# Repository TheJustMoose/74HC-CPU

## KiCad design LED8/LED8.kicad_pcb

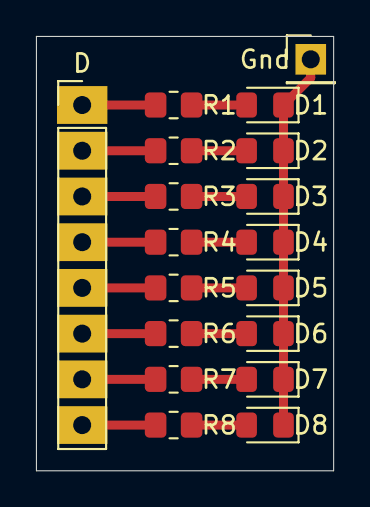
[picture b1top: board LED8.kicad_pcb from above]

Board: 2 copper layers, 16.5 x 24.1 mm, 18 parts (0 on the bottom side), 17 nets.

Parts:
D: Conn_01x08_Male; PinHeader_1x08_P2.54mm_Vertical
D1, D2, D3, D4, D5, D6, D7, D8: LED; LED_0805_2012Metric_Pad1.15x1.40mm_HandSolder
Gnd: Conn_01x01_Male; PinHeader_1x01_P2.54mm_Vertical
R1, R2, R3, R4, R5, R6, R7, R8: 1k; R_0805_2012Metric_Pad1.20x1.40mm_HandSolder

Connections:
unnamed: D1.1, D2.1, D3.1, D4.1, D5.1, D6.1, D7.1, D8.1, Gnd.1
unnamed: D1.2, R1.1
unnamed: D2.2, R2.1
unnamed: D3.2, R3.1
unnamed: D4.2, R4.1
unnamed: D5.2, R5.1
unnamed: D6.2, R6.1
unnamed: D7.2, R7.1
unnamed: D8.2, R8.1
unnamed: D.1, R1.2
unnamed: D.2, R2.2
unnamed: D.3, R3.2
unnamed: D.4, R4.2
unnamed: D.5, R5.2
unnamed: D.6, R6.2
unnamed: D.7, R7.2
unnamed: D.8, R8.2

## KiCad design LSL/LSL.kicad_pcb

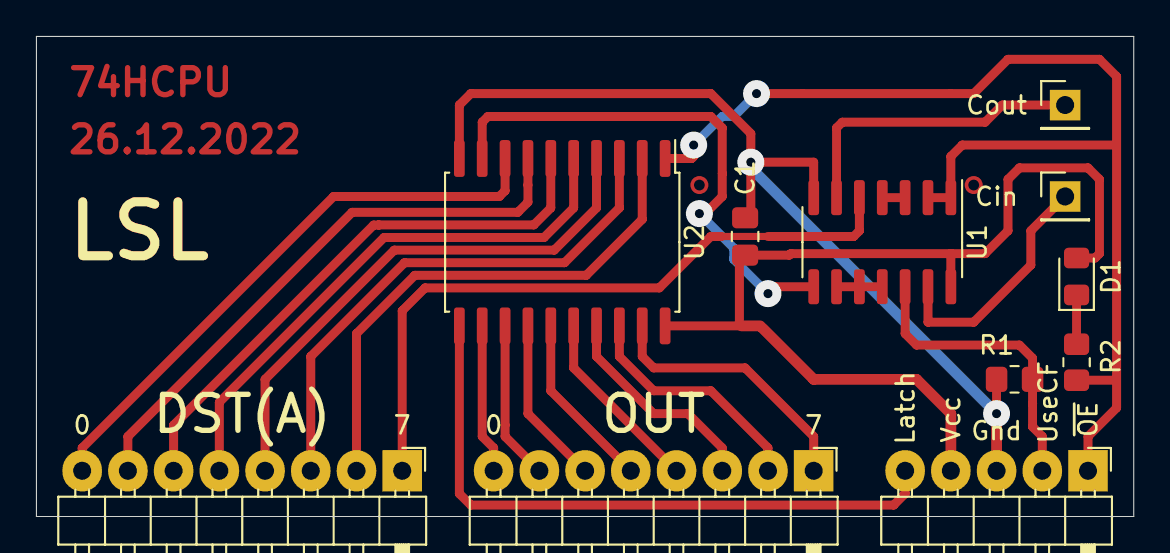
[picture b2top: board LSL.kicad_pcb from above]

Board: 2 copper layers, 61.0 x 26.7 mm, 11 parts (0 on the bottom side), 27 nets.

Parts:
C1: 0.1uF; C_0805_2012Metric_Pad1.18x1.45mm_HandSolder
D1: LED; LED_0805_2012Metric_Pad1.15x1.40mm_HandSolder
J1, J4: Conn_01x01_Male; PinHeader_1x01_P2.54mm_Vertical
J2, J3: Conn_01x08_Male; PinHeader_1x08_P2.54mm_Horizontal
J5: Conn_01x05_Male; PinHeader_1x05_P2.54mm_Horizontal
R1, R2: R; R_0805_2012Metric_Pad1.20x1.40mm_HandSolder
U1: 74HC00; SO-14_3.9x8.65mm_P1.27mm
U2: 74LS573; SOIC-20W_7.5x12.8mm_P1.27mm

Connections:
/CF_IN: J4.1, U1.13
/D0: J2.8, U2.8
/D1: J2.7, U2.7
/D2: J2.6, U2.6
/D3: J2.5, U2.5
/D4: J2.4, U2.4
/D5: J2.3, U2.3
/D6: J2.2, U2.2
/D7: J2.1, U1.5
/Latch: J5.5, U2.11
/O0: J3.8, U2.12
/O1: J3.7, U2.13
/O2: J3.6, U2.14
/O3: J3.5, U2.15
/O4: J3.4, U2.16
/O5: J3.3, U2.17
/O6: J3.2, U2.18
/O7: J3.1, U2.19
/UseCF: J5.2, R1.1, U1.12
/~(CF&OE): J1.1, U1.6
/~OE: J5.1, R2.2, U1.1, U1.2, U2.1
GND: C1.2, J5.3, R1.2, U1.7, U2.10
unnamed: D1.1, R2.1
unnamed: U1.3, U1.4
unnamed: U1.8, U2.9
unnamed: U1.9, U1.10, U1.11
VCC: C1.1, D1.2, J5.4, U1.14, U2.20

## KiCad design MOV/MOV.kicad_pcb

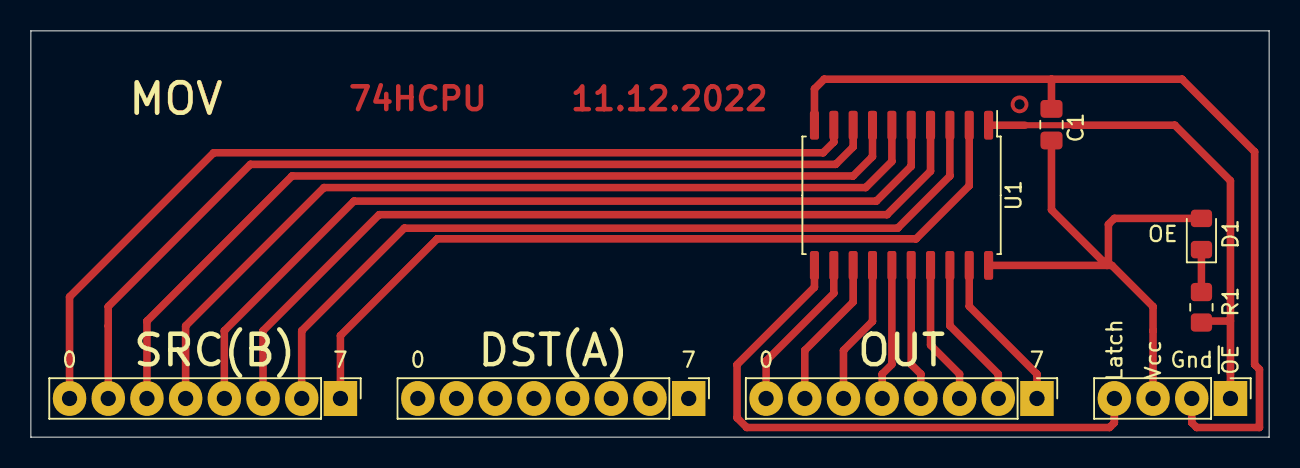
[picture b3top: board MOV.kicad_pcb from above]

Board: 2 copper layers, 81.3 x 26.7 mm, 8 parts (0 on the bottom side), 21 nets.

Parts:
C1: 0.1uF; C_0805_2012Metric_Pad1.18x1.45mm_HandSolder
D1: LED; LED_0805_2012Metric_Pad1.15x1.40mm_HandSolder
J1, J2, J3: Conn_01x08_Male; PinHeader_1x08_P2.54mm_Vertical
J4: Conn_01x04_Male; PinHeader_1x04_P2.54mm_Vertical
R1: 1k; R_0805_2012Metric_Pad1.20x1.40mm_HandSolder
U1: 74LS573; SOP-20_7.5x12.8mm_P1.27mm

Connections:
/B0: J1.8, U1.9
/B7: J1.1, U1.2
/Latch: J4.4, U1.11
/OUT0: J3.8, U1.12
/OUT7: J3.1, U1.19
/~OE: J4.1, R1.2, U1.1
GND: C1.2, J4.2, U1.10
unnamed: D1.1, R1.1
unnamed: J1.2, U1.3
unnamed: J1.3, U1.4
unnamed: J1.4, U1.5
unnamed: J1.5, U1.6
unnamed: J1.6, U1.7
unnamed: J1.7, U1.8
unnamed: J3.2, U1.18
unnamed: J3.3, U1.17
unnamed: J3.4, U1.16
unnamed: J3.5, U1.15
unnamed: J3.6, U1.14
unnamed: J3.7, U1.13
VCC: C1.1, D1.2, J4.3, U1.20

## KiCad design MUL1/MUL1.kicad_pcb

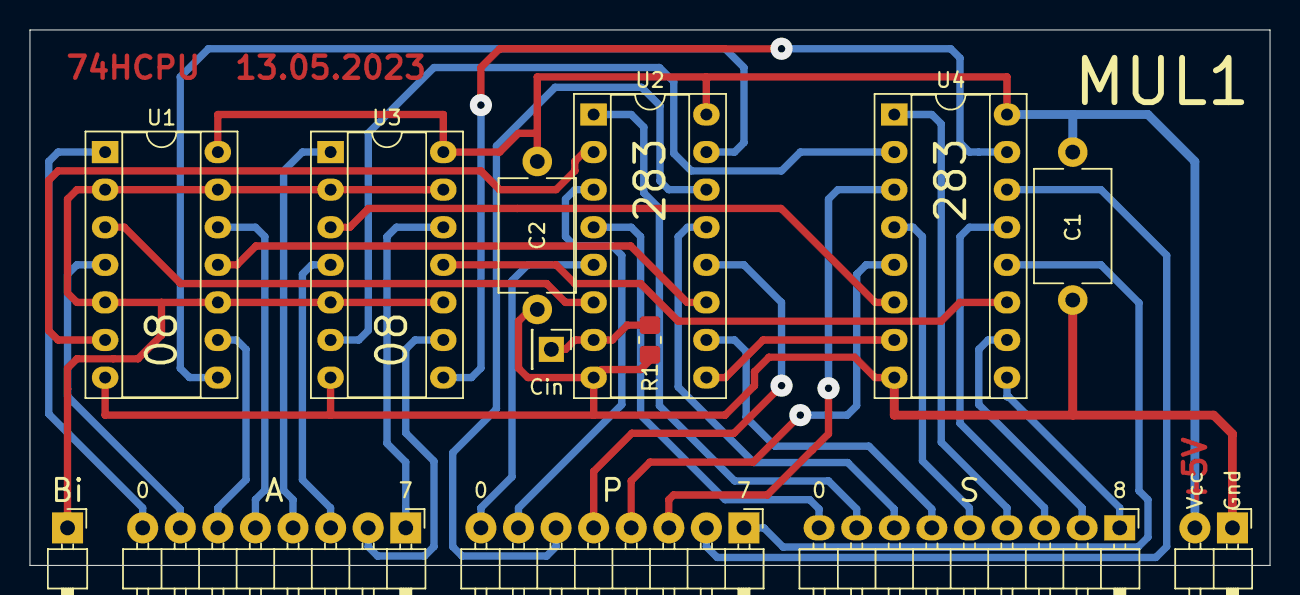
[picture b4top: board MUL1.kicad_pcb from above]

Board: 2 copper layers, 83.8 x 36.2 mm, 13 parts (0 on the bottom side), 38 nets.

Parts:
C1, C2: 0.1uF; C_Disc_D7.5mm_W5.0mm_P10.00mm
J1, J3: Conn_01x08_Male; PinHeader_1x08_P2.54mm_Horizontal
J2: Conn_01x09_Male; PinHeader_1x09_P2.54mm_Horizontal
J4: Conn_01x01_Male; PinHeader_1x01_P2.54mm_Horizontal
J5: Conn_01x02_Male; PinHeader_1x02_P2.54mm_Horizontal
J6: Conn_01x01_Male; PinHeader_1x01_P2.54mm_Vertical
R1: 10k; R_0805_2012Metric_Pad1.20x1.40mm_HandSolder
U1, U3: 74LS08; DIP-14_W7.62mm_Socket
U2, U4: 74LS283; DIP-16_W7.62mm_Socket

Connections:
/A0: J3.8, U1.1
/A1: J3.7, U1.4
/A2: J3.6, U1.9
/A3: J3.5, U1.12
/A4: J3.4, U3.1
/A5: J3.3, U3.4
/A6: J3.2, U3.9
/A7: J3.1, U3.12
/Bi: J4.1, U1.2, U1.5, U1.10, U1.13, U3.2, U3.5, U3.10, U3.13
/P0: J1.8, U2.5
/P1: J1.7, U2.3
/P2: J1.6, U2.14
/P3: J1.5, U2.12
/P4: J1.4, U4.5
/P5: J1.3, U4.3
/P6: J1.2, U4.14
/P7: J1.1, U4.12
/S0: J2.9, U2.4
/S1: J2.8, U2.1
/S2: J2.7, U2.13
/S3: J2.6, U2.10
/S4: J2.5, U4.4
/S5: J2.4, U4.1
/S6: J2.3, U4.13
/S7: J2.2, U4.10
/S8: J2.1, U4.9
GND: C1.2, C2.2, J5.1, R1.1, U1.7, U2.8, U3.7, U4.8
unnamed: J6.1, R1.2, U2.7
unnamed: U1.3, U2.6
unnamed: U1.6, U2.2
unnamed: U1.8, U2.15
unnamed: U1.11, U2.11
unnamed: U2.9, U4.7
unnamed: U3.3, U4.6
unnamed: U3.6, U4.2
unnamed: U3.8, U4.15
unnamed: U3.11, U4.11
VCC: C1.1, C2.1, J5.2, U1.14, U2.16, U3.14, U4.16

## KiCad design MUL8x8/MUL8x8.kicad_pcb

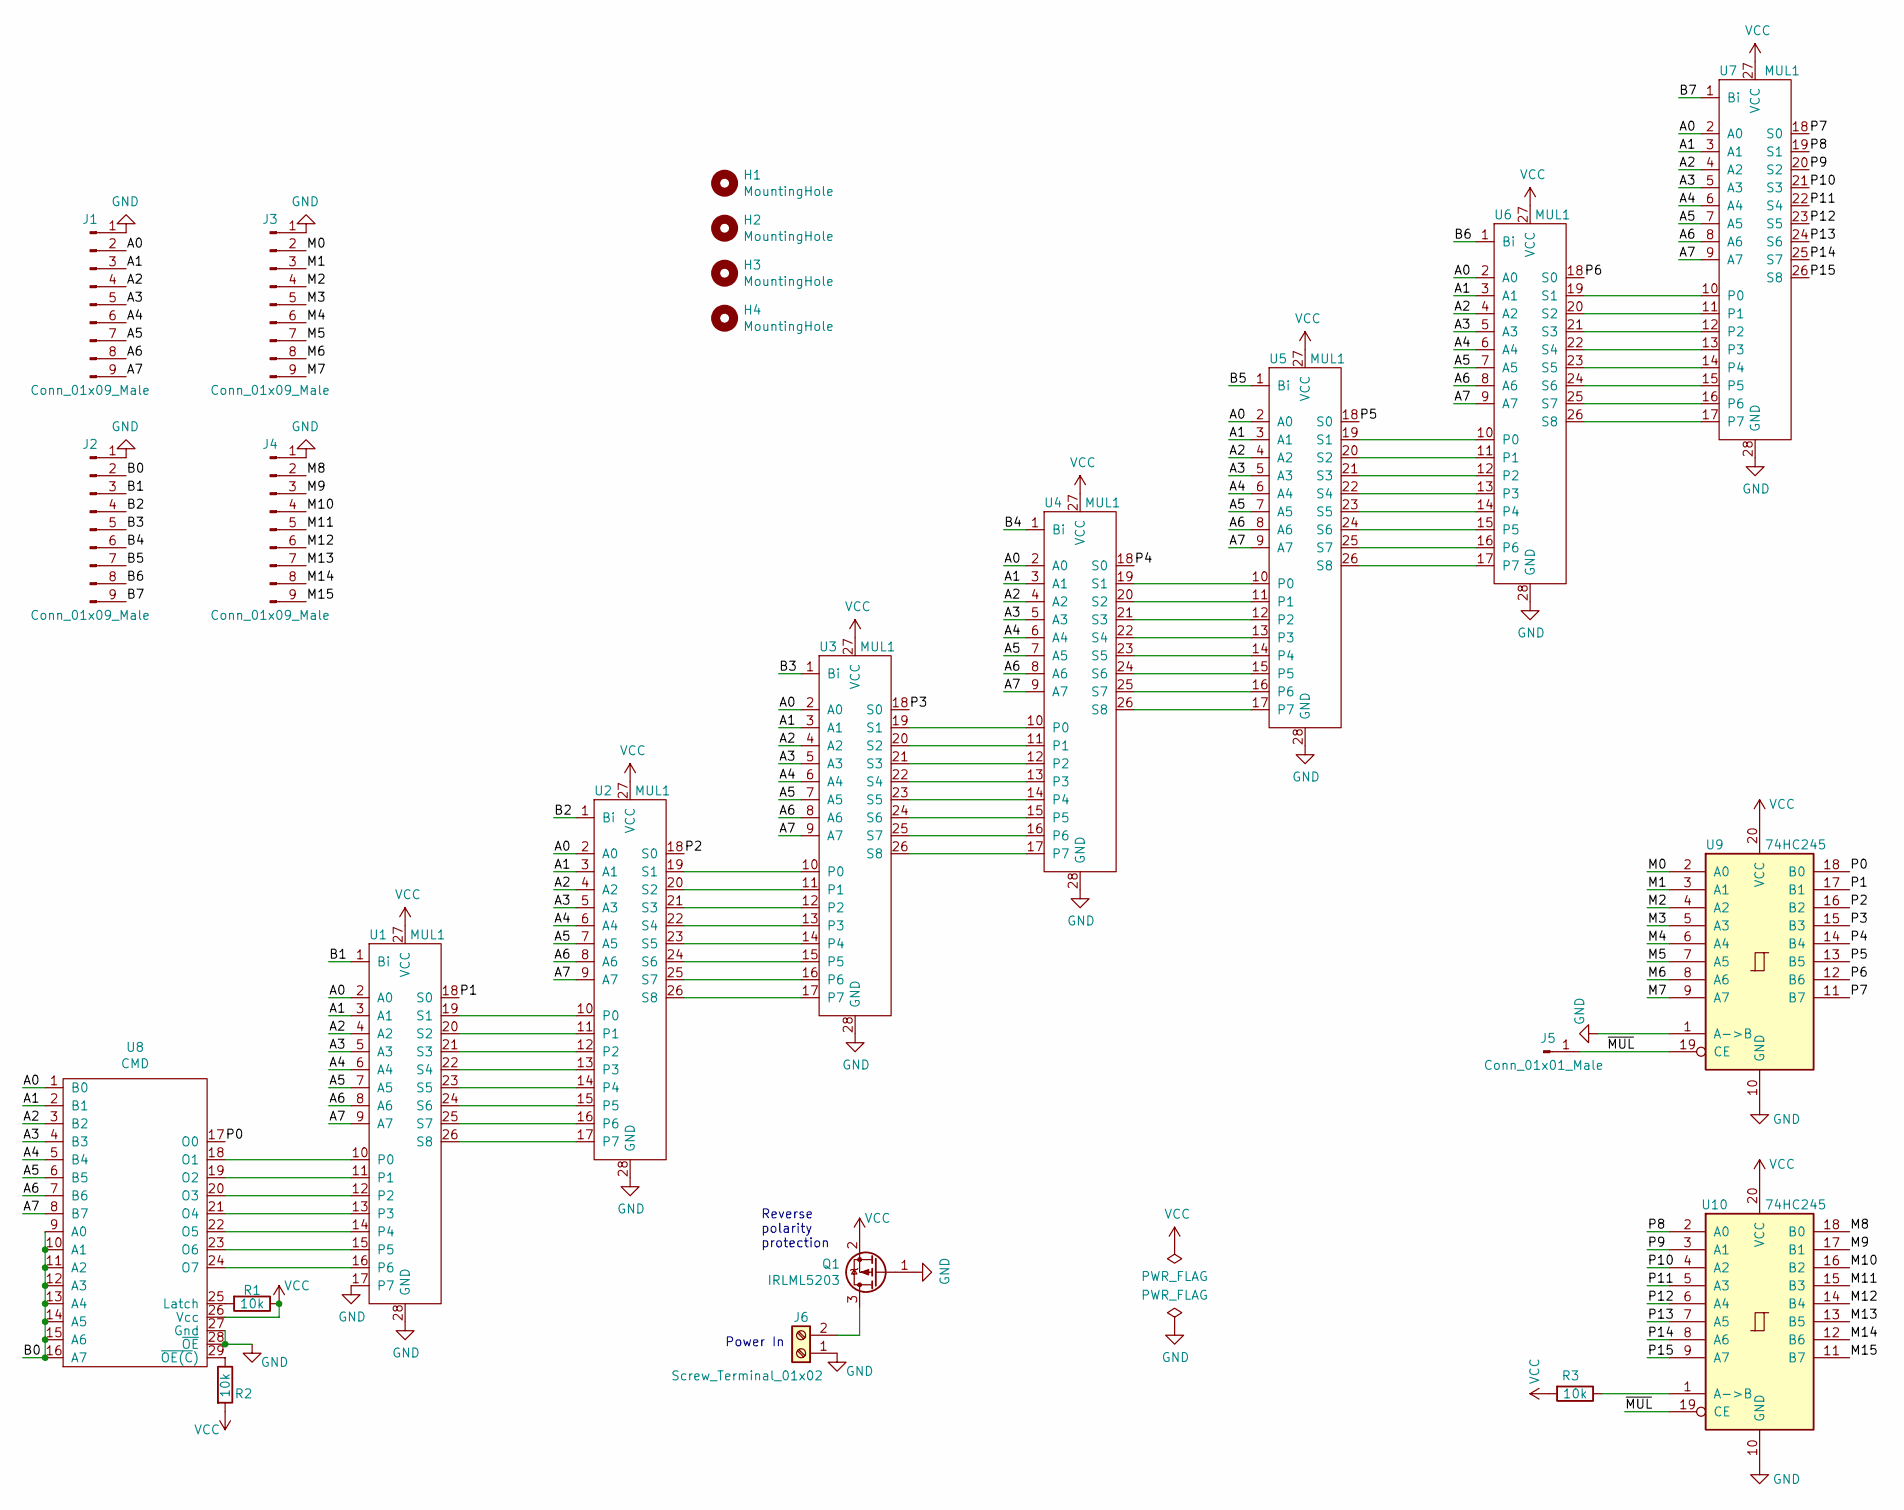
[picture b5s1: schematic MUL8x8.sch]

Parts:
H1, H2, H3, H4: MountingHole; MountingHole_3.2mm_M3
J1, J2, J3, J4: Conn_01x09_Male; PinHeader_1x09_P2.54mm_Vertical
J5: Conn_01x01_Male; PinHeader_1x01_P2.54mm_Vertical
J6: Screw_Terminal_01x02; TerminalBlock_Phoenix_MKDS-1,5-2_1x02_P5.00mm_Horizontal
Q1: IRLML5203; SOT-23
R1, R2, R3: 10k; R_0805_2012Metric_Pad1.20x1.40mm_HandSolder
U1, U2, U3, U4, U5, U6, U7: MUL1
U8: CMD
U9, U10: 74HC245; DIP-20_W7.62mm_Socket

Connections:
/A0: J1.2, U1.2 (A0), U2.2 (A0), U3.2 (A0), U4.2 (A0), U5.2 (A0), U6.2 (A0), U7.2 (A0), U8.1 (B0)
/A1: J1.3, U1.3 (A1), U2.3 (A1), U3.3 (A1), U4.3 (A1), U5.3 (A1), U6.3 (A1), U7.3 (A1), U8.2 (B1)
/A2: J1.4, U1.4 (A2), U2.4 (A2), U3.4 (A2), U4.4 (A2), U5.4 (A2), U6.4 (A2), U7.4 (A2), U8.3 (B2)
/A3: J1.5, U1.5 (A3), U2.5 (A3), U3.5 (A3), U4.5 (A3), U5.5 (A3), U6.5 (A3), U7.5 (A3), U8.4 (B3)
/A4: J1.6, U1.6 (A4), U2.6 (A4), U3.6 (A4), U4.6 (A4), U5.6 (A4), U6.6 (A4), U7.6 (A4), U8.5 (B4)
/A5: J1.7, U1.7 (A5), U2.7 (A5), U3.7 (A5), U4.7 (A5), U5.7 (A5), U6.7 (A5), U7.7 (A5), U8.6 (B5)
/A6: J1.8, U1.8 (A6), U2.8 (A6), U3.8 (A6), U4.8 (A6), U5.8 (A6), U6.8 (A6), U7.8 (A6), U8.7 (B6)
/A7: J1.9, U1.9 (A7), U2.9 (A7), U3.9 (A7), U4.9 (A7), U5.9 (A7), U6.9 (A7), U7.9 (A7), U8.8 (B7)
/B0: J2.2, U8.9 (A0), U8.10 (A1), U8.11 (A2), U8.12 (A3), U8.13 (A4), U8.14 (A5), U8.15 (A6), U8.16 (A7)
/B1: J2.3, U1.1 (Bi)
/B2: J2.4, U2.1 (Bi)
/B3: J2.5, U3.1 (Bi)
/B4: J2.6, U4.1 (Bi)
/B5: J2.7, U5.1 (Bi)
/B6: J2.8, U6.1 (Bi)
/B7: J2.9, U7.1 (Bi)
/M0: J3.2, U9.2 (A0)
/M1: J3.3, U9.3 (A1)
/M2: J3.4, U9.4 (A2)
/M3: J3.5, U9.5 (A3)
/M4: J3.6, U9.6 (A4)
/M5: J3.7, U9.7 (A5)
/M6: J3.8, U9.8 (A6)
/M7: J3.9, U9.9 (A7)
/M8: J4.2, U10.18 (B0)
/M9: J4.3, U10.17 (B1)
/M10: J4.4, U10.16 (B2)
/M11: J4.5, U10.15 (B3)
/M12: J4.6, U10.14 (B4)
/M13: J4.7, U10.13 (B5)
/M14: J4.8, U10.12 (B6)
/M15: J4.9, U10.11 (B7)
/P0: U8.17 (O0), U9.18 (B0)
/P1: U1.18 (S0), U9.17 (B1)
/P2: U2.18 (S0), U9.16 (B2)
/P3: U3.18 (S0), U9.15 (B3)
/P4: U4.18 (S0), U9.14 (B4)
/P5: U5.18 (S0), U9.13 (B5)
/P6: U6.18 (S0), U9.12 (B6)
/P7: U7.18 (S0), U9.11 (B7)
/P8: U7.19 (S1), U10.2 (A0)
/P9: U7.20 (S2), U10.3 (A1)
/P10: U7.21 (S3), U10.4 (A2)
/P11: U7.22 (S4), U10.5 (A3)
/P12: U7.23 (S5), U10.6 (A4)
/P13: U7.24 (S6), U10.7 (A5)
/P14: U7.25 (S7), U10.8 (A6)
/P15: U7.26 (S8), U10.9 (A7)
/~MUL: J5.1, U9.19 (CE), U10.19 (CE)
GND: J1.1, J2.1, J3.1, J4.1, J6.1, Q1.1 (G), U1.17 (P7), U1.28 (GND), U2.28 (GND), U3.28 (GND), U4.28 (GND), U5.28 (GND), U6.28 (GND), U7.28 (GND), U8.27 (Gnd), U8.28 (~OE), U9.1 (A->B), U9.10 (GND), U10.10 (GND)
unnamed: J6.2, Q1.3 (D)
unnamed: R1.2, U8.25 (Latch)
unnamed: R2.1, U8.29 (~OE(C))
unnamed: R3.1, U10.1 (A->B)
unnamed: U1.10 (P0), U8.18 (O1)
unnamed: U1.11 (P1), U8.19 (O2)
unnamed: U1.12 (P2), U8.20 (O3)
unnamed: U1.13 (P3), U8.21 (O4)
unnamed: U1.14 (P4), U8.22 (O5)
unnamed: U1.15 (P5), U8.23 (O6)
unnamed: U1.16 (P6), U8.24 (O7)
unnamed: U1.19 (S1), U2.10 (P0)
unnamed: U1.20 (S2), U2.11 (P1)
unnamed: U1.21 (S3), U2.12 (P2)
unnamed: U1.22 (S4), U2.13 (P3)
unnamed: U1.23 (S5), U2.14 (P4)
unnamed: U1.24 (S6), U2.15 (P5)
unnamed: U1.25 (S7), U2.16 (P6)
unnamed: U1.26 (S8), U2.17 (P7)
unnamed: U2.19 (S1), U3.10 (P0)
unnamed: U2.20 (S2), U3.11 (P1)
unnamed: U2.21 (S3), U3.12 (P2)
unnamed: U2.22 (S4), U3.13 (P3)
unnamed: U2.23 (S5), U3.14 (P4)
unnamed: U2.24 (S6), U3.15 (P5)
unnamed: U2.25 (S7), U3.16 (P6)
unnamed: U2.26 (S8), U3.17 (P7)
unnamed: U3.19 (S1), U4.10 (P0)
unnamed: U3.20 (S2), U4.11 (P1)
unnamed: U3.21 (S3), U4.12 (P2)
unnamed: U3.22 (S4), U4.13 (P3)
unnamed: U3.23 (S5), U4.14 (P4)
unnamed: U3.24 (S6), U4.15 (P5)
unnamed: U3.25 (S7), U4.16 (P6)
unnamed: U3.26 (S8), U4.17 (P7)
unnamed: U4.19 (S1), U5.10 (P0)
unnamed: U4.20 (S2), U5.11 (P1)
unnamed: U4.21 (S3), U5.12 (P2)
unnamed: U4.22 (S4), U5.13 (P3)
unnamed: U4.23 (S5), U5.14 (P4)
unnamed: U4.24 (S6), U5.15 (P5)
unnamed: U4.25 (S7), U5.16 (P6)
unnamed: U4.26 (S8), U5.17 (P7)
unnamed: U5.19 (S1), U6.10 (P0)
unnamed: U5.20 (S2), U6.11 (P1)
unnamed: U5.21 (S3), U6.12 (P2)
unnamed: U5.22 (S4), U6.13 (P3)
unnamed: U5.23 (S5), U6.14 (P4)
unnamed: U5.24 (S6), U6.15 (P5)
unnamed: U5.25 (S7), U6.16 (P6)
unnamed: U5.26 (S8), U6.17 (P7)
unnamed: U6.19 (S1), U7.10 (P0)
unnamed: U6.20 (S2), U7.11 (P1)
unnamed: U6.21 (S3), U7.12 (P2)
unnamed: U6.22 (S4), U7.13 (P3)
unnamed: U6.23 (S5), U7.14 (P4)
unnamed: U6.24 (S6), U7.15 (P5)
unnamed: U6.25 (S7), U7.16 (P6)
unnamed: U6.26 (S8), U7.17 (P7)
VCC: Q1.2 (S), R1.1, R2.2, R3.2, U1.27 (VCC), U2.27 (VCC), U3.27 (VCC), U4.27 (VCC), U5.27 (VCC), U6.27 (VCC), U7.27 (VCC), U8.26 (Vcc), U9.20 (VCC), U10.20 (VCC)

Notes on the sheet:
Reverse polarity protection
Power In

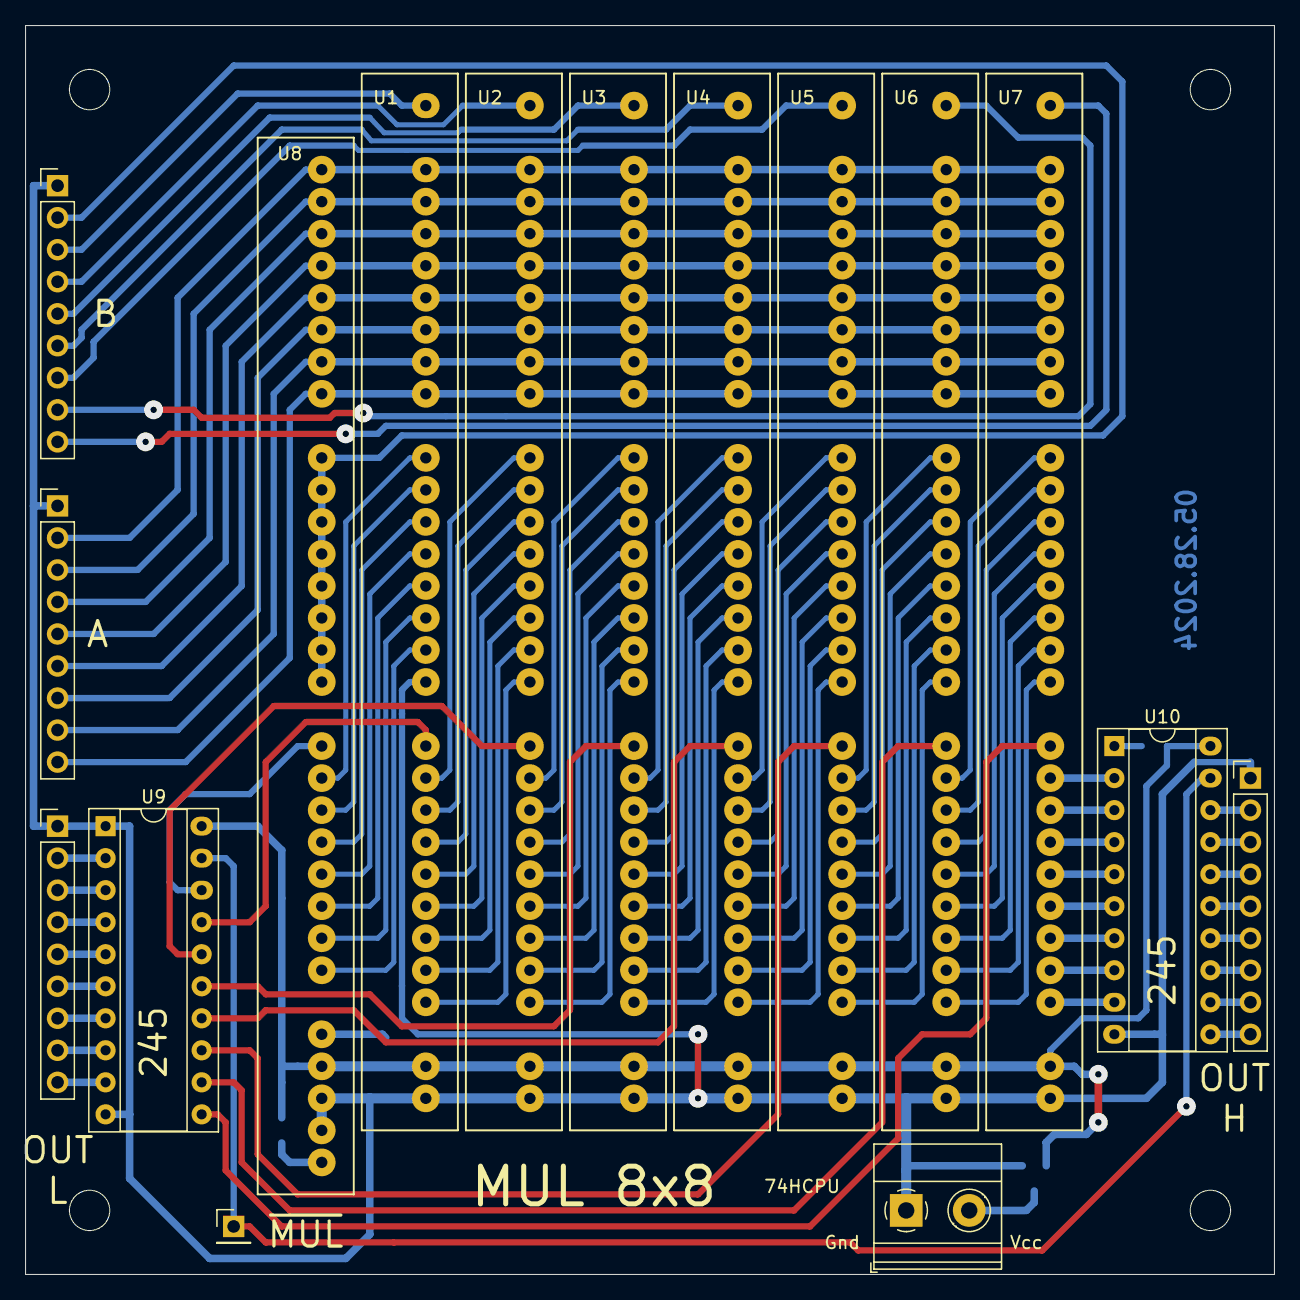
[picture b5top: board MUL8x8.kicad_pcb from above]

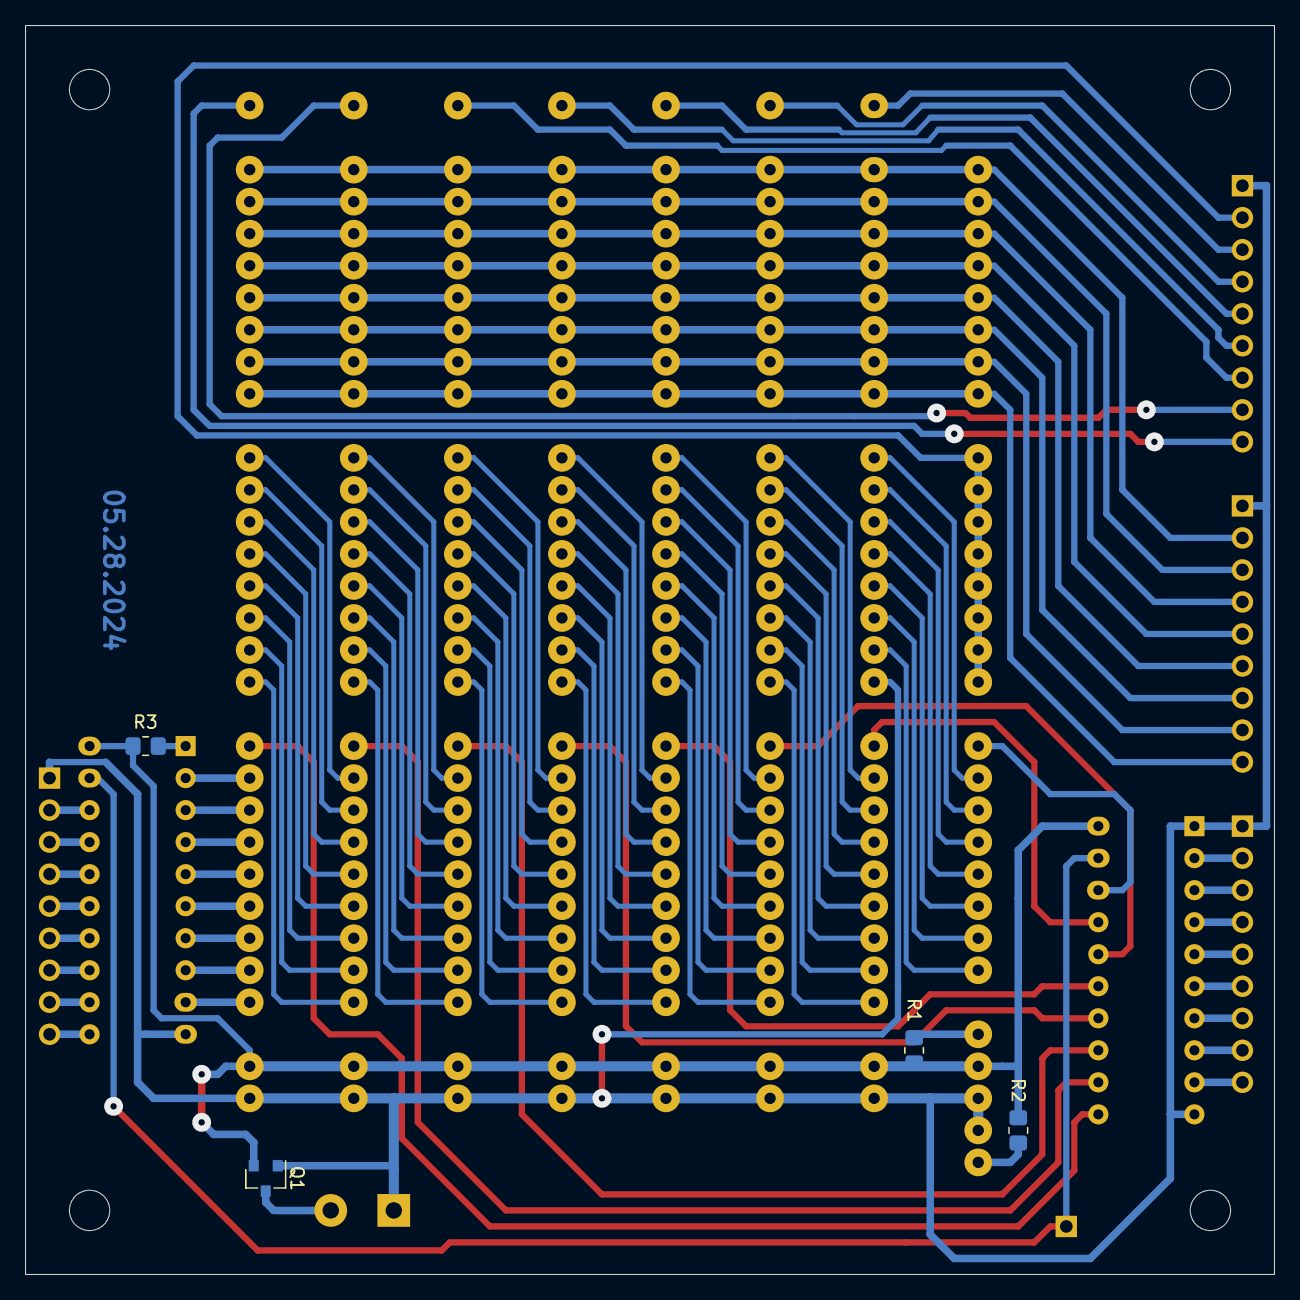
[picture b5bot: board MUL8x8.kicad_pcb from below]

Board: 2 copper layers, 99.1 x 99.1 mm, 24 parts (4 on the bottom side), 110 nets.

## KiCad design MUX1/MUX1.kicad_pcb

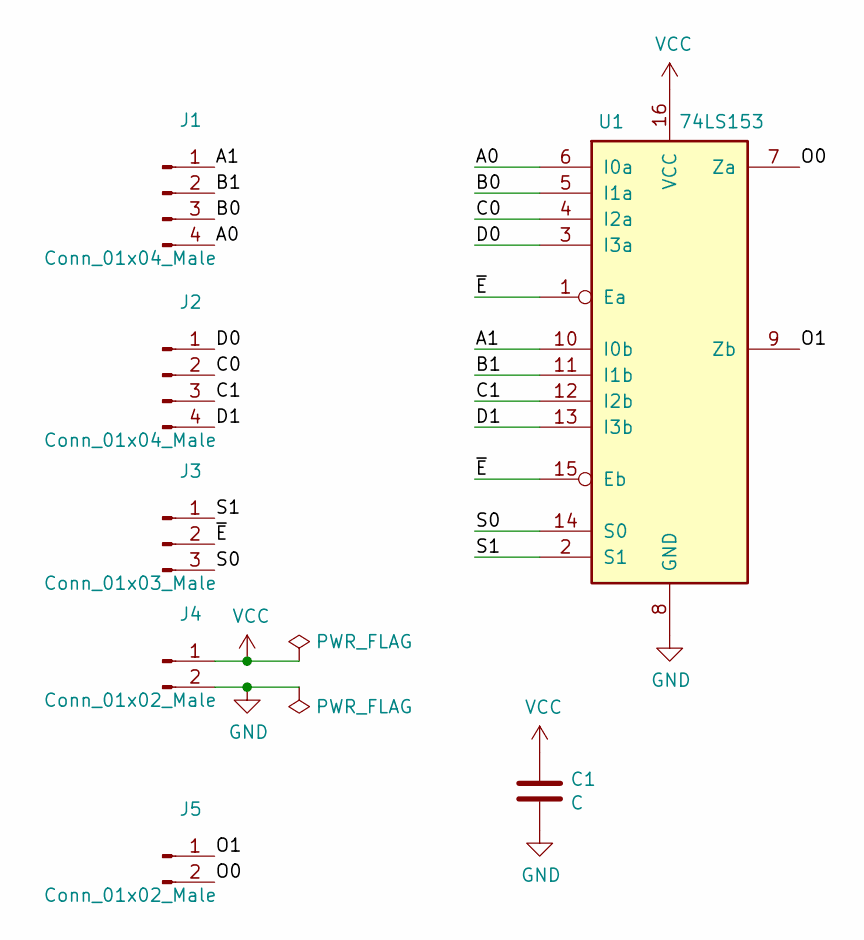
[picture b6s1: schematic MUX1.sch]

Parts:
C1: C; C_0805_2012Metric_Pad1.18x1.45mm_HandSolder
J1, J2: Conn_01x04_Male; PinHeader_1x04_P2.54mm_Horizontal
J3: Conn_01x03_Male; PinHeader_1x03_P2.54mm_Horizontal
J4, J5: Conn_01x02_Male; PinHeader_1x02_P2.54mm_Horizontal
U1: 74LS153; SO-16_3.9x9.9mm_P1.27mm

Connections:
/A0: J1.4, U1.6 (I0a)
/A1: J1.1, U1.10 (I0b)
/B0: J1.3, U1.5 (I1a)
/B1: J1.2, U1.11 (I1b)
/C0: J2.2, U1.4 (I2a)
/C1: J2.3, U1.12 (I2b)
/D0: J2.1, U1.3 (I3a)
/D1: J2.4, U1.13 (I3b)
/O0: J5.2, U1.7 (Za)
/O1: J5.1, U1.9 (Zb)
/S0: J3.3, U1.14 (S0)
/S1: J3.1, U1.2 (S1)
/~E: J3.2, U1.1 (Ea), U1.15 (Eb)
GND: C1.2, J4.2, U1.8 (GND)
VCC: C1.1, J4.1, U1.16 (VCC)

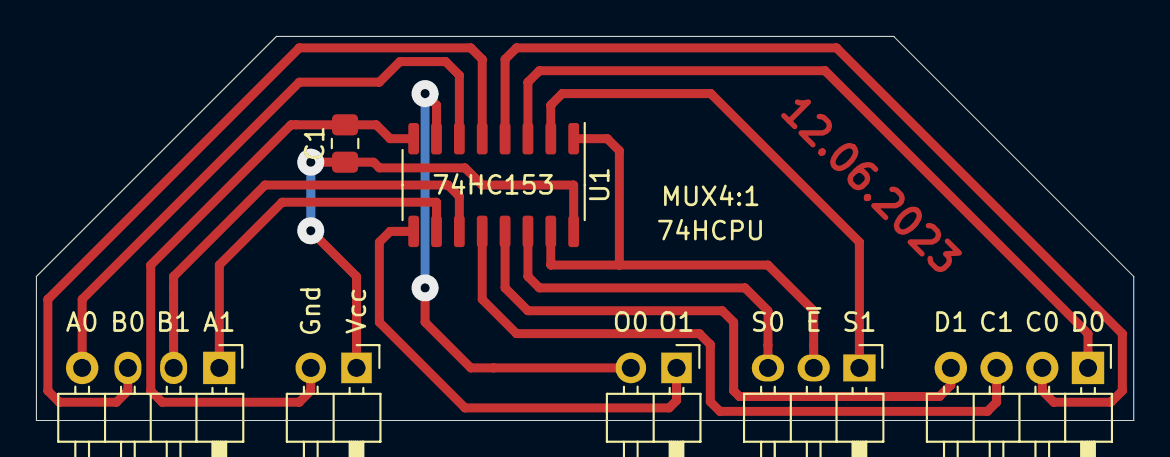
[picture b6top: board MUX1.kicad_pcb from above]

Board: 2 copper layers, 61.0 x 21.3 mm, 7 parts (0 on the bottom side), 15 nets.

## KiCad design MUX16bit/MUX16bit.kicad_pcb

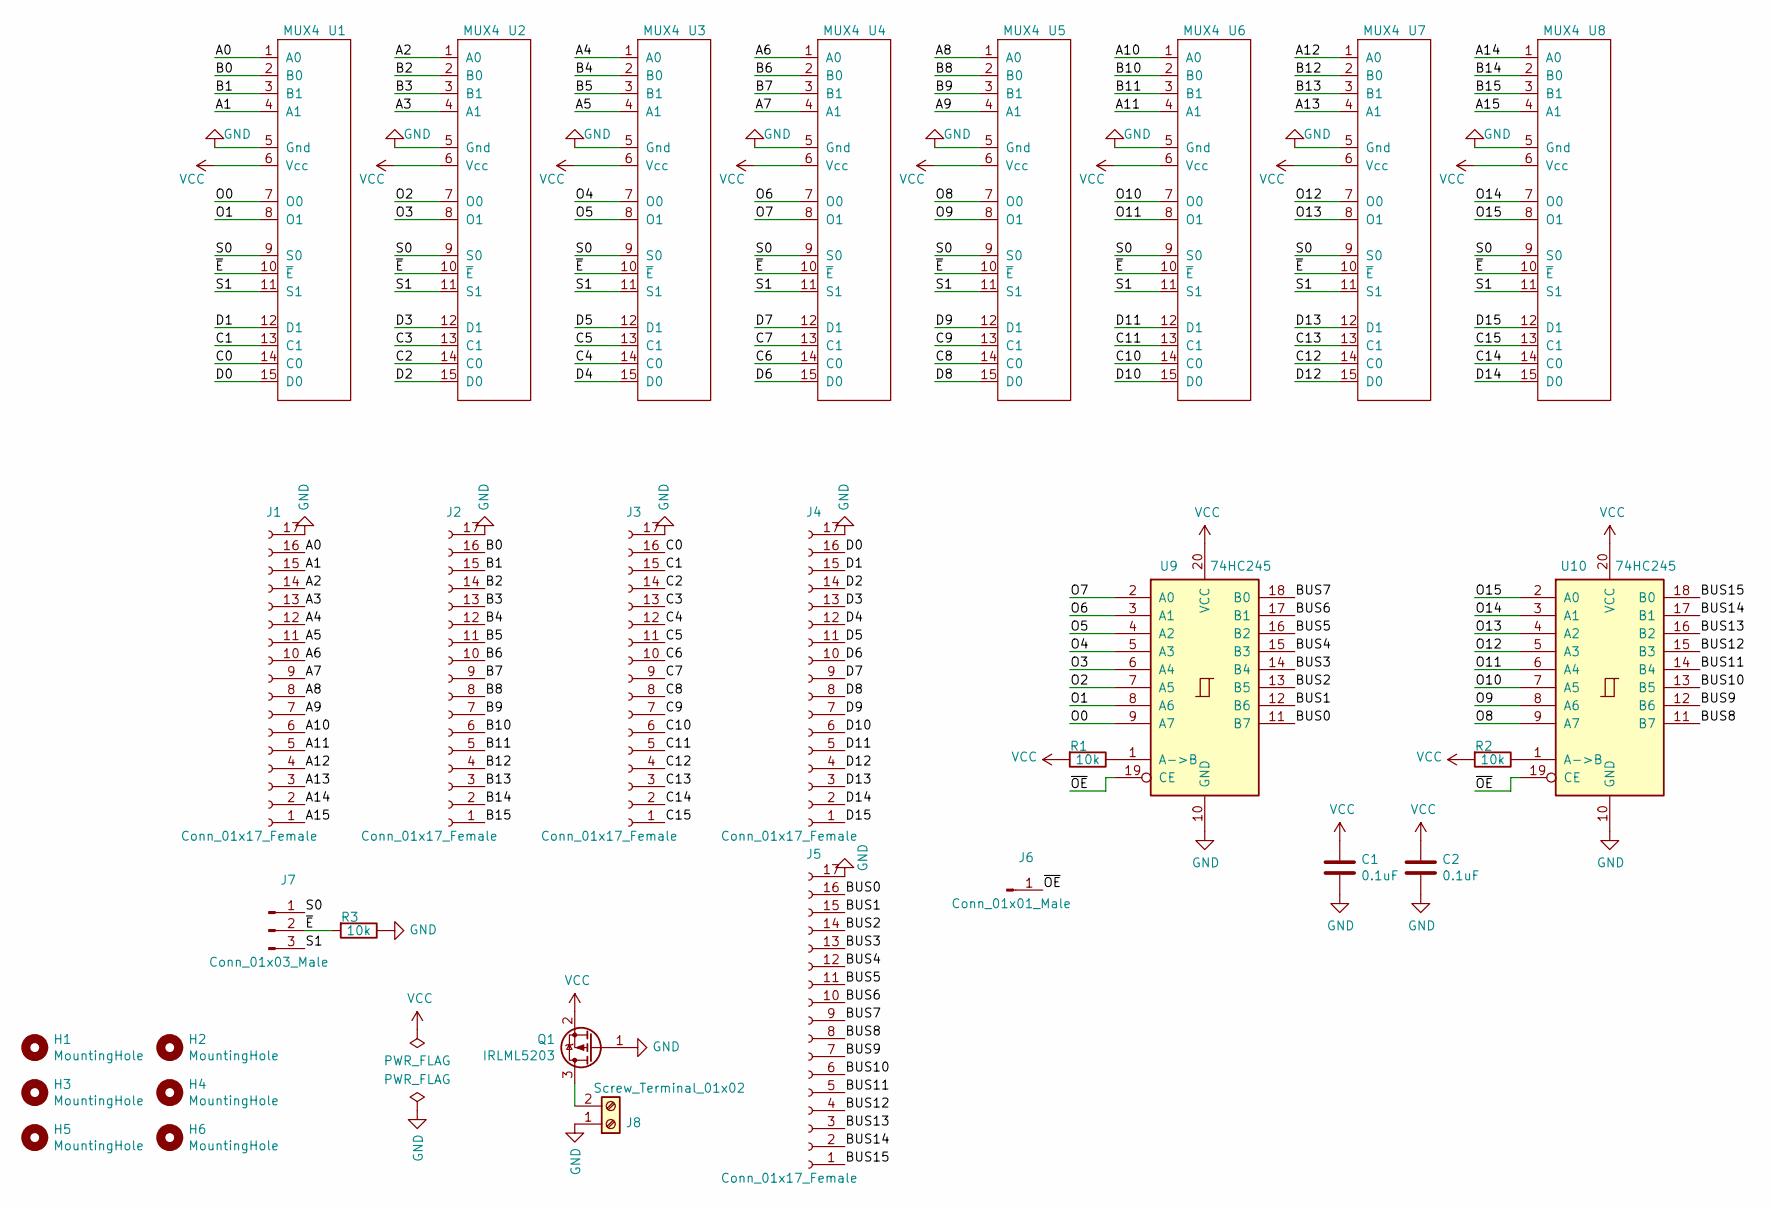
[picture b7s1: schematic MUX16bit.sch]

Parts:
C1, C2: 0.1uF; C_0805_2012Metric_Pad1.18x1.45mm_HandSolder
H1, H2, H3, H4, H5, H6: MountingHole; MountingHole_3.2mm_M3
J1, J2, J3, J4, J5: Conn_01x17_Female; PinSocket_1x17_P2.54mm_Vertical
J6: Conn_01x01_Male; PinHeader_1x01_P2.54mm_Vertical
J7: Conn_01x03_Male; PinHeader_1x03_P2.54mm_Vertical
J8: Screw_Terminal_01x02; TerminalBlock_Phoenix_PT-1,5-2-5.0-H_1x02_P5.00mm_Horizontal
Q1: IRLML5203; SOT-23
R1, R2, R3: 10k; R_0805_2012Metric_Pad1.20x1.40mm_HandSolder
U1, U2, U3, U4, U5, U6, U7, U8: MUX4; MUX1
U9, U10: 74HC245; SOIC-20W_7.5x12.8mm_P1.27mm

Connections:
/A0: J1.16, U1.1 (A0)
/A1: J1.15, U1.4 (A1)
/A2: J1.14, U2.1 (A0)
/A3: J1.13, U2.4 (A1)
/A4: J1.12, U3.1 (A0)
/A5: J1.11, U3.4 (A1)
/A6: J1.10, U4.1 (A0)
/A7: J1.9, U4.4 (A1)
/A8: J1.8, U5.1 (A0)
/A9: J1.7, U5.4 (A1)
/A10: J1.6, U6.1 (A0)
/A11: J1.5, U6.4 (A1)
/A12: J1.4, U7.1 (A0)
/A13: J1.3, U7.4 (A1)
/A14: J1.2, U8.1 (A0)
/A15: J1.1, U8.4 (A1)
/B0: J2.16, U1.2 (B0)
/B1: J2.15, U1.3 (B1)
/B2: J2.14, U2.2 (B0)
/B3: J2.13, U2.3 (B1)
/B4: J2.12, U3.2 (B0)
/B5: J2.11, U3.3 (B1)
/B6: J2.10, U4.2 (B0)
/B7: J2.9, U4.3 (B1)
/B8: J2.8, U5.2 (B0)
/B9: J2.7, U5.3 (B1)
/B10: J2.6, U6.2 (B0)
/B11: J2.5, U6.3 (B1)
/B12: J2.4, U7.2 (B0)
/B13: J2.3, U7.3 (B1)
/B14: J2.2, U8.2 (B0)
/B15: J2.1, U8.3 (B1)
/BUS0: J5.16, U9.11 (B7)
/BUS1: J5.15, U9.12 (B6)
/BUS2: J5.14, U9.13 (B5)
/BUS3: J5.13, U9.14 (B4)
/BUS4: J5.12, U9.15 (B3)
/BUS5: J5.11, U9.16 (B2)
/BUS6: J5.10, U9.17 (B1)
/BUS7: J5.9, U9.18 (B0)
/BUS8: J5.8, U10.11 (B7)
/BUS9: J5.7, U10.12 (B6)
/BUS10: J5.6, U10.13 (B5)
/BUS11: J5.5, U10.14 (B4)
/BUS12: J5.4, U10.15 (B3)
/BUS13: J5.3, U10.16 (B2)
/BUS14: J5.2, U10.17 (B1)
/BUS15: J5.1, U10.18 (B0)
/C0: J3.16, U1.14 (C0)
/C1: J3.15, U1.13 (C1)
/C2: J3.14, U2.14 (C0)
/C3: J3.13, U2.13 (C1)
/C4: J3.12, U3.14 (C0)
/C5: J3.11, U3.13 (C1)
/C6: J3.10, U4.14 (C0)
/C7: J3.9, U4.13 (C1)
/C8: J3.8, U5.14 (C0)
/C9: J3.7, U5.13 (C1)
/C10: J3.6, U6.14 (C0)
/C11: J3.5, U6.13 (C1)
/C12: J3.4, U7.14 (C0)
/C13: J3.3, U7.13 (C1)
/C14: J3.2, U8.14 (C0)
/C15: J3.1, U8.13 (C1)
/D0: J4.16, U1.15 (D0)
/D1: J4.15, U1.12 (D1)
/D2: J4.14, U2.15 (D0)
/D3: J4.13, U2.12 (D1)
/D4: J4.12, U3.15 (D0)
/D5: J4.11, U3.12 (D1)
/D6: J4.10, U4.15 (D0)
/D7: J4.9, U4.12 (D1)
/D8: J4.8, U5.15 (D0)
/D9: J4.7, U5.12 (D1)
/D10: J4.6, U6.15 (D0)
/D11: J4.5, U6.12 (D1)
/D12: J4.4, U7.15 (D0)
/D13: J4.3, U7.12 (D1)
/D14: J4.2, U8.15 (D0)
/D15: J4.1, U8.12 (D1)
/O0: U1.7 (O0), U9.9 (A7)
/O1: U1.8 (O1), U9.8 (A6)
/O2: U2.7 (O0), U9.7 (A5)
/O3: U2.8 (O1), U9.6 (A4)
/O4: U3.7 (O0), U9.5 (A3)
/O5: U3.8 (O1), U9.4 (A2)
/O6: U4.7 (O0), U9.3 (A1)
/O7: U4.8 (O1), U9.2 (A0)
/O8: U5.7 (O0), U10.9 (A7)
/O9: U5.8 (O1), U10.8 (A6)
/O10: U6.7 (O0), U10.7 (A5)
/O11: U6.8 (O1), U10.6 (A4)
/O12: U7.7 (O0), U10.5 (A3)
/O13: U7.8 (O1), U10.4 (A2)
/O14: U8.7 (O0), U10.3 (A1)
/O15: U8.8 (O1), U10.2 (A0)
/S0: J7.1, U1.9 (S0), U2.9 (S0), U3.9 (S0), U4.9 (S0), U5.9 (S0), U6.9 (S0), U7.9 (S0), U8.9 (S0)
/S1: J7.3, U1.11 (S1), U2.11 (S1), U3.11 (S1), U4.11 (S1), U5.11 (S1), U6.11 (S1), U7.11 (S1), U8.11 (S1)
/~E: J7.2, R3.2, U1.10 (~E), U2.10 (~E), U3.10 (~E), U4.10 (~E), U5.10 (~E), U6.10 (~E), U7.10 (~E), U8.10 (~E)
/~OE: J6.1, U9.19 (CE), U10.19 (CE)
GND: C1.2, C2.2, J1.17, J2.17, J3.17, J4.17, J5.17, J8.1, Q1.1 (G), R3.1, U1.5 (Gnd), U2.5 (Gnd), U3.5 (Gnd), U4.5 (Gnd), U5.5 (Gnd), U6.5 (Gnd), U7.5 (Gnd), U8.5 (Gnd), U9.10 (GND), U10.10 (GND)
unnamed: J8.2, Q1.3 (D)
unnamed: R1.1, U9.1 (A->B)
unnamed: R2.1, U10.1 (A->B)
VCC: C1.1, C2.1, Q1.2 (S), R1.2, R2.2, U1.6 (Vcc), U2.6 (Vcc), U3.6 (Vcc), U4.6 (Vcc), U5.6 (Vcc), U6.6 (Vcc), U7.6 (Vcc), U8.6 (Vcc), U9.20 (VCC), U10.20 (VCC)

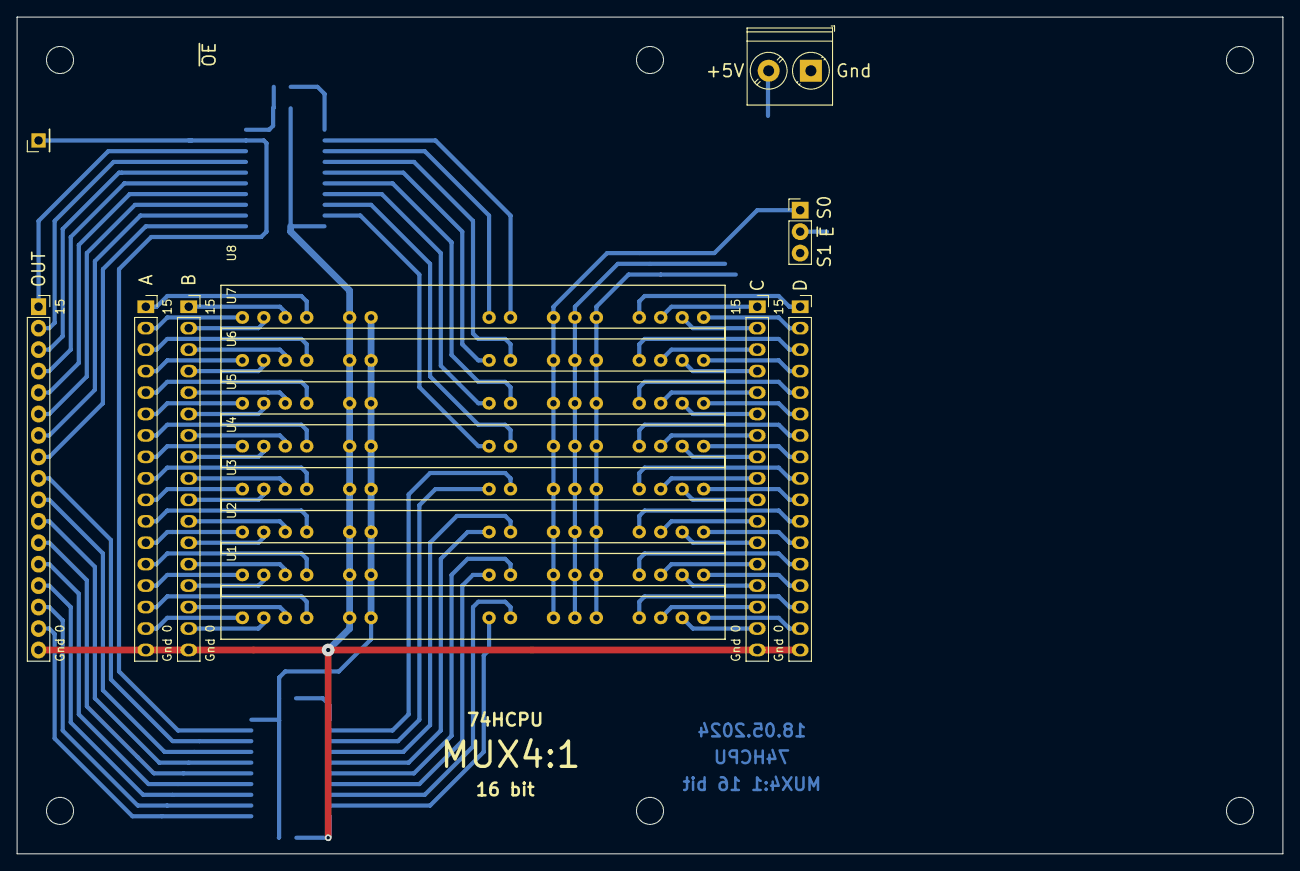
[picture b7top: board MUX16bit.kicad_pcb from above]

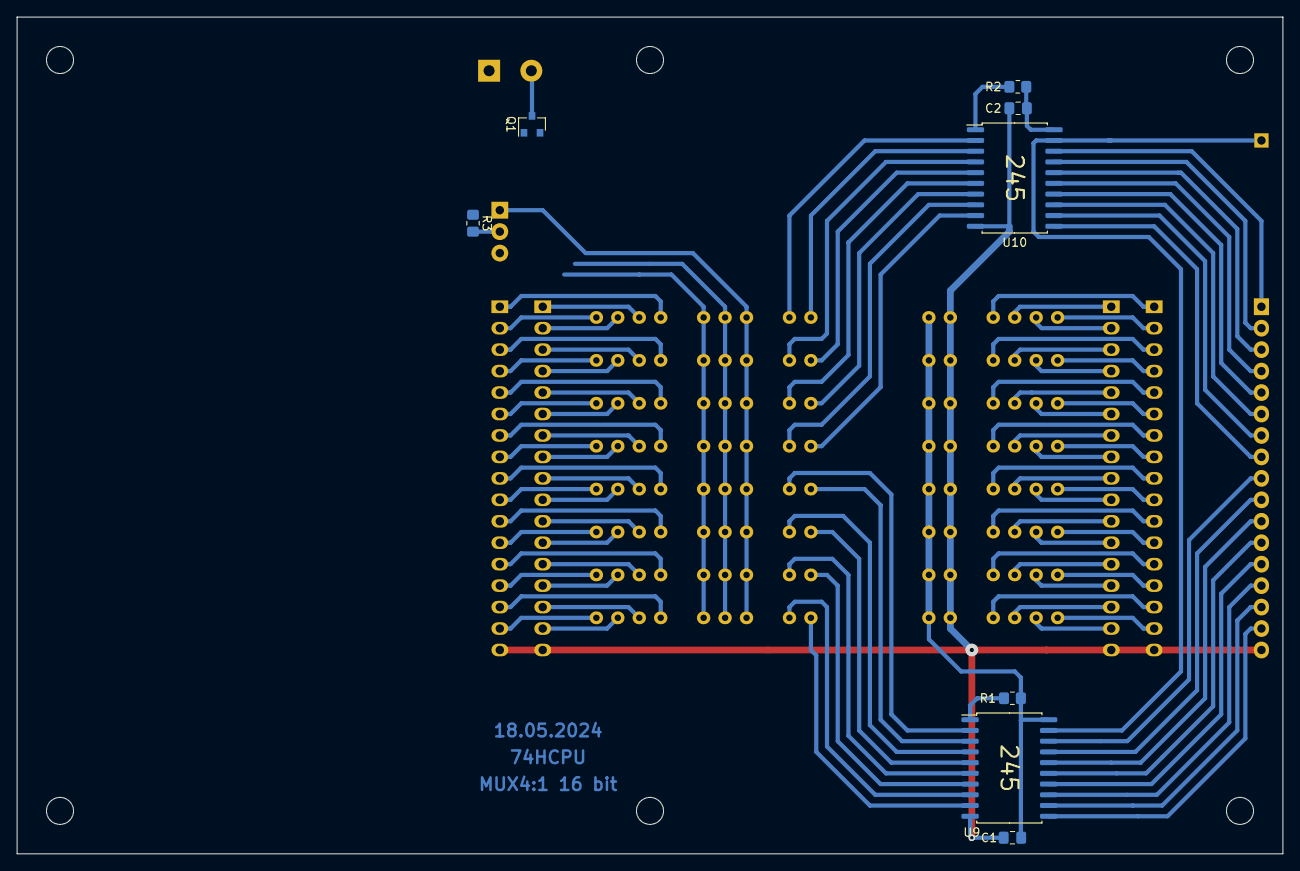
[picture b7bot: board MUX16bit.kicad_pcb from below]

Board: 2 copper layers, 149.9 x 99.1 mm, 30 parts (8 on the bottom side), 105 nets.
